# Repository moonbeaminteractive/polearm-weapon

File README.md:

# polearm-weapon
pole rod staff based weapon for short range area events

##Concept: 
Wand/rod is a weapon which can cast three different kinds of spells by sending sound signals to the vest. The kind of spell is visualized by the led strip on the wand. There will be deplay between each spell, and the delay time can be shortened by one of the pickups. In order to cast a spell, the player has to both swing the rod to activate it and push one of the three buttons to cast a specific type of spell. 

##Software: 

Prerequisite libraries:  <br/>
Statistic.h  <br/>
Adafruit_DotStar.h <br/>

Statistic.h: calculates the swing variance of the gyro sensor  <br/>
Adafruit_DotStar.h: controls the RGB lighting on the led strip  <br/>

The software continuously polls the 3 rod buttons (red, green, blue) to select a spell. <br/>
Also, it continuously logs ADXL accelerometer data in blocks of 100 values and calculates the variance of the samples. Using the variance instead of the raw values allows the tracking of rapid wand motions to cast a spell, no matter what the initial direction of the wand is. <br/>

When casting each spell, the DotStar LEDs light up with the respective color (blue for the blue button, red for the red button, green for the green button) to conveniently visualize which spell has been selected. Additional functionality is implemented to drive a buzzer with a frequency that depends on the spell that is casted. For the red spell, a buzzer tone with period of 100 ms is generated, for the green a tone with 200 ms period is generated, and for the blue a tone with 300 ms period is generated. <br/>

Time-sensitive functions of the code have been implemented with the millis() function to avoid blocking that the delay() function introduces. <br/>

##Usage Settings:
Current settings:<br/>
Default blockout - 30 seconds (slow recharge)<br/>
Blockout with pickup - 10 seconds (faster boosted recharge)<br/>

When a weapon booster pickup is correctly attached, the wand flashes 5 times to notify the user that it has detected and activated it. The wand glows a default yellow color when active, and whenever a spell is castable. If it is timed out, on blockout after casting a spell, all lights on the wand will switch off until it is recharged again. On casting a spell, the wand glows the same color as the spell.<br/>

To use, plug in a USB-A to USB-B connector between the wand and the vest.<br/>

##Hardware: 
1 x gyro sensor <br/>
1 x magnetic buzzer <br/>
1 x dotstar led strip <br/>
1 x arduino mini <br/>
3 x push button <br/>
1 x USB-B <br/>

Gyro sensor: detects if the rod is activated or not. Player will swing the rod to activate the weapon <br/>
Magnetic buzzer: sends sound signal to receivers installed on vests <br/>
Dotstar led strip: displays which spell just casted by the player (r, g, b) <br/>
Push button: each color of the push button (r, g, b) will send a different kind of spells <br/>
USB-B: receives serial information from the vest for shorter spell recharge delay <br/>

##Circuit and PCB Design Process: 
We started with a very simple board – an Arduino Uno, an infrared emitter, a push button and a led strip. Then we improved it by adding more components and functionalities to the board – we added a tilt sensor switch for activation, a 6 degree of freedom sensor, a Piezo buzzer for casting different spells, a nrf24l01 for Bluetooth communication, and replaced the Arduino Uno with Arduino Pro Mini. In the next phase, we replaced the 6 degree of freedom sensor with a gyro sensor and removed the tilt switch as we decided to only use swing behavior to activate the wand, which could be achieved by just using the gyro sensor. We also added three kinds of buttons, imaging the player can perform different kinds of combinations of buttons for different spells. Then we moved on to the communication with the other parts. We realized that it would work the best if we communicated with the vest directly using serial via TX/RX pins instead of Bluetooth. Finally, the design we have right now has a USB-B for serial communication with the vest, removing the Bluetooth module. 

In order to fit the PCB into the wand, we wanted to limit its width to around 3.5 cm. We decided to put the gyro sensor and buzzer at the top of the wand for more accurate measurement. The initial PCB design was just about 3.6 cm. Matt helped us to produce the final design, which used the small resistor and a more compact layout to reduce the width to 3.4 cm. It also added two transistors for 5.0 V power supply. These tiny resistors and transistors saved lots of space for PCB design.

###Circuit

###PCB

###Fabrication Design: 
The design of weapon was in lowpoly style and we have a good rationale for the design.

The sytle of the design is futuristic overall and lowpoly design fits in the game.
Using lowpoly design, we are able to build three-dimensional objects by two dimensional materials like paper by folding them. In this way, we are able to put whatever electronics and PCB boards into it without destroying the idea of the weapon being a wand.
The design was generated by sketching, modelling and finally drawings. The tools used were Illustrator, Rhino and special thanks to Clement, whose tools helped with generating joints for the design.

As for the prototyping, We laser cut (using Epilog Mini Laser Cutter) the design using chipboard.

For the materials, we hesitated between plastic, yupo paper, chipboard as well as metal. Eventually, due to cost, the feasibility of laser cutting as well as the imagined final demonstration, we decided to have black chipboards serving as surfaces.

The output of laser film printer appears some errors because of mechanical manufacture and different settings of power and speed. The drawings were drawn in both AutoCAD and Illustrator. Dimensions in drawings were decided by both measurements and repetitive trail and error.

A challenge we encountered was to fit in the PCB boards and placing buttons, electronics at the right position, which wasted a lot of trails and time.

Deciding settings of power and speed was another challenge for us. Although each material corresponds to its suggested settings, materials produced by different manufacturers perform differently under the same setting. We kept adjusting the settings to cut through acrylic sheets but at the same time prevent it from melting and blackening. The final prototype was actually our fifth version of printing..

###Paper Prototype:

###Final Wand:

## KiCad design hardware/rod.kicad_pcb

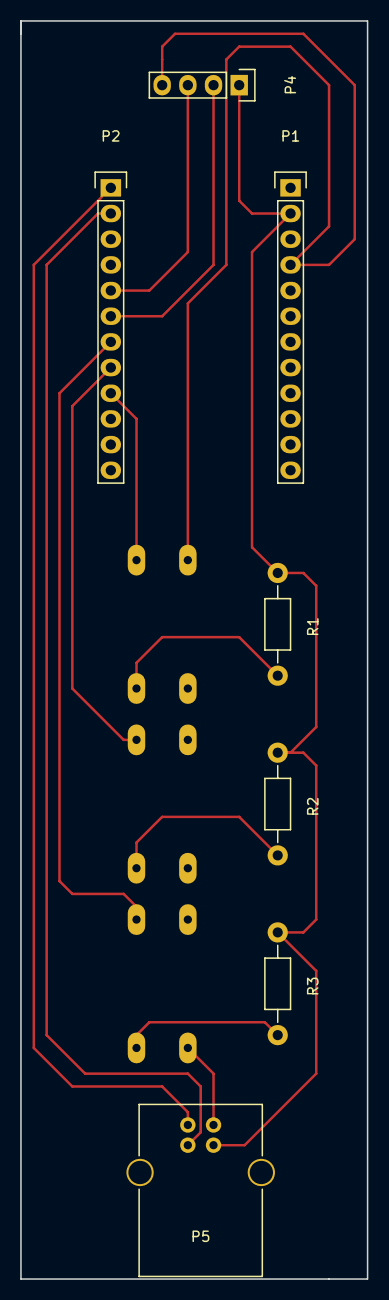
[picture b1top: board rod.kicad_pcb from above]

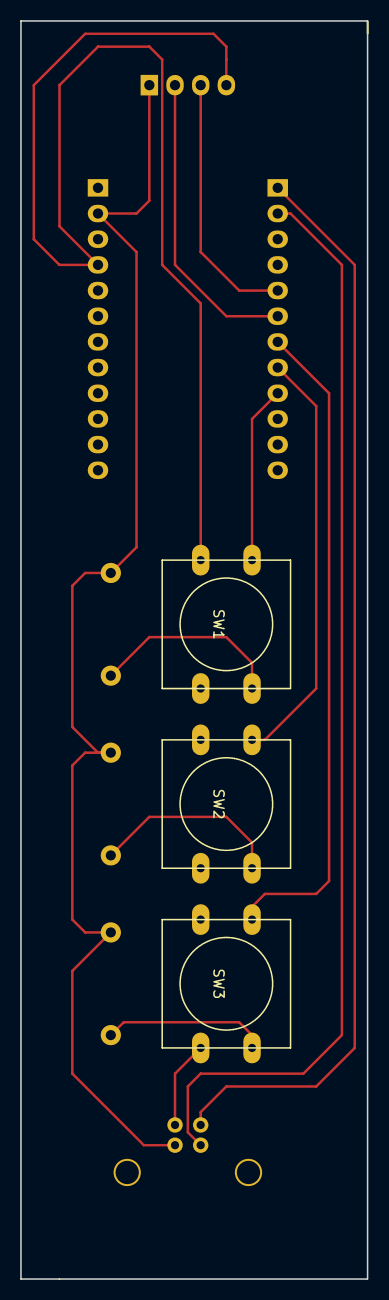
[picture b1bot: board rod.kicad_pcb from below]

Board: 2 copper layers, 34.3 x 124.5 mm, 10 parts (3 on the bottom side), 9 nets.

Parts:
P1, P2: arduino_mini; Pin_Header_Straight_1x12
P4: DOTSTAR; Pin_Header_Straight_1x04
P5: USB_B
R1, R2, R3: R; Resistor_Horizontal_RM10mm
SW1: SW_PUSH_R; SW_PUSH-12mm
SW2: SW_PUSH_B; SW_PUSH-12mm
SW3: SW_PUSH_G; SW_PUSH-12mm

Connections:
2: P2.5, P4.3
3: P2.6, P4.2
4: P2.7, R3.2, SW3.2
5: P2.8, R2.2, SW2.2
6: P2.9, R1.2, SW1.2
GND: P1.2, P4.1, P5.4, R1.1, R2.1, R3.1
PWR: P1.4, P4.4, P5.1, SW1.1, SW2.1, SW3.1
RX: P2.2, P5.3
TX: P2.1, P5.2

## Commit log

2016-11-13 added folders
2016-11-13 replaced gitignore with empty txt
2016-12-02 send/receive signal
    send r/g/b color text to another arduino on clicking r/g/b button
2016-12-06 add current schematics and pcb
2016-12-06 softwareserial code
2016-12-08 fixed DotStar color issue
2016-12-08 implement spells, counts, and frequencies
2016-12-08 Updated PCB
2016-12-08 "Updated PCB"
2016-12-08 bak file created
2016-12-11 3.6cm width pcb
2016-12-12 comment out changed made by edith
2016-12-13 updated semi-final version of rod pcb schematics and layout
2016-12-14 added blockout logic for the 3 spells
2016-12-15 Create Design
2016-12-15 About
2016-12-15 Rename about to readme.md
2016-12-15 Designdrawing
2016-12-15 model
2016-12-15 paperprototype
2016-12-15 Some updates and debugging. Deactivate want when spell not castable. Refactored code.
2016-12-15 presentation
2016-12-15 sketch
2016-12-17 Final Wand
2016-12-18 final code. changed to delay/timeout based recharge instead of number of spells. Added other edits too for feedback.
2016-12-18 added usage settings to wand readme
